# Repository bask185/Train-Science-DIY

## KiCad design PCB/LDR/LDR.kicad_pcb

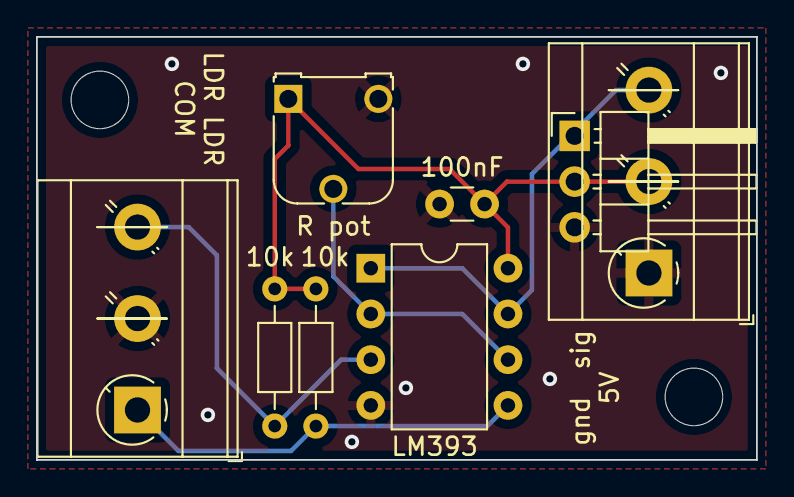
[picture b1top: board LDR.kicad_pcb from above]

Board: 2 copper layers, 40.0 x 23.5 mm, 8 parts (0 on the bottom side), 6 nets.

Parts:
C: 100nF; C_Disc_D3.0mm_W1.6mm_P2.50mm
J1101: LDR; TerminalBlock_MetzConnect_Type073_RT02603HBLU_1x03_P5.08mm_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
J1102: ter; PinHeader_1x03_P2.54mm_Horizontal
J1103: ter; TerminalBlock_MetzConnect_Type073_RT02603HBLU_1x03_P5.08mm_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
R1101, R1102: 10k; R_Axial_DIN0204_L3.6mm_D1.6mm_P7.62mm_Horizontal
R pot: REF; Potentiometer_Runtron_RM-065_Vertical
U1101: LM393; DIP-8_W7.62mm

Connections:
+5V: C.1, J1102.2, J1103.2, R1101.1, R1102.1, R pot.1, U1101.8 (V+)
GND: C.2, J1101.2, J1102.3, J1103.1, R pot.3, U1101.4 (V-)
unnamed: J1101.1, R1101.2, U1101.5 (+)
unnamed: J1101.3, R1102.2, U1101.3 (+)
unnamed: J1102.1, J1103.3, U1101.1, U1101.7
unnamed: R pot.2, U1101.2 (-), U1101.6 (-)

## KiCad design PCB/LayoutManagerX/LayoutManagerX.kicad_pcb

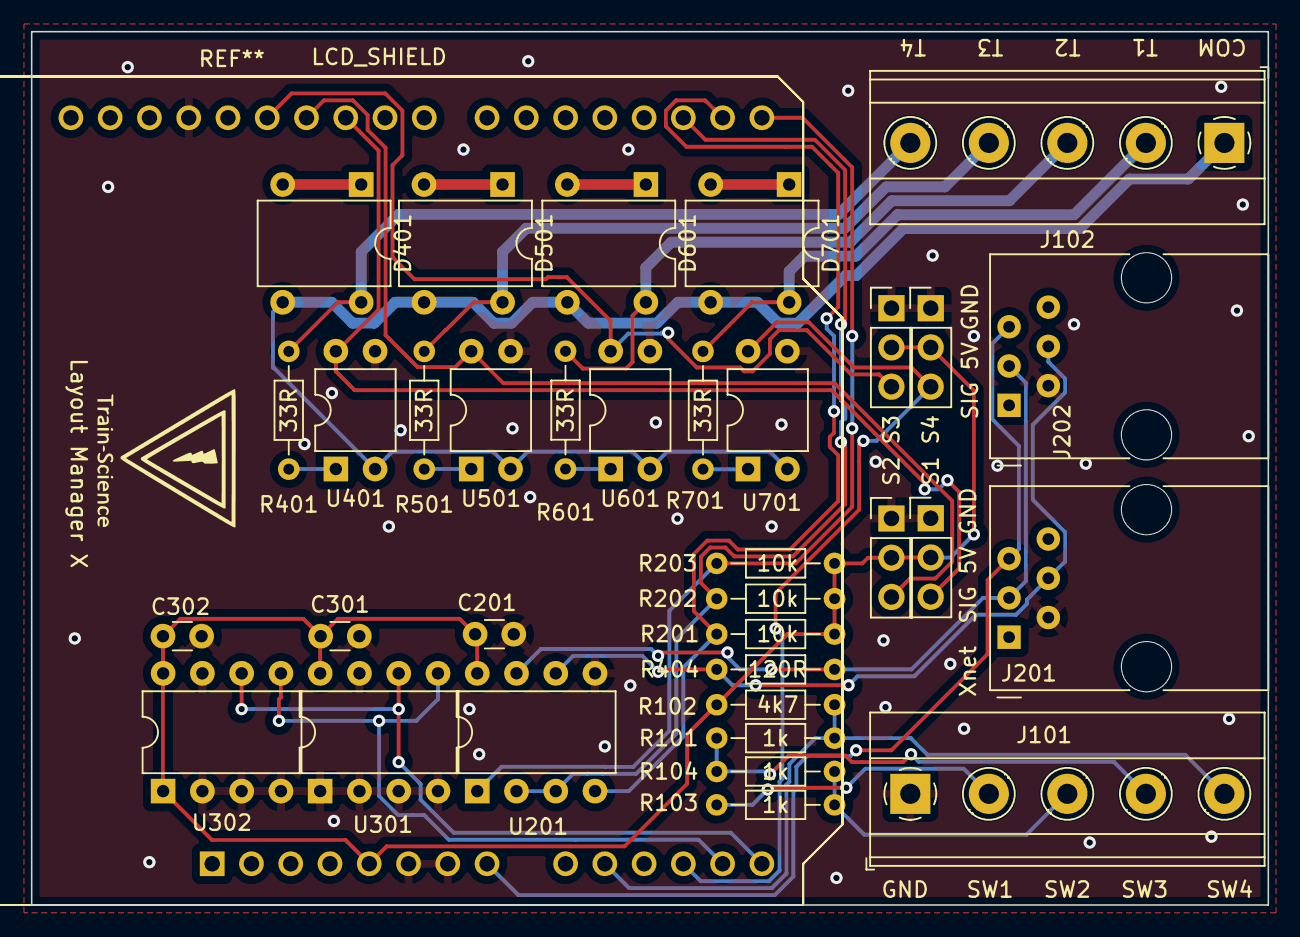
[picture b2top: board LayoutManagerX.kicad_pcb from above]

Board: 2 copper layers, 80.0 x 56.5 mm, 36 parts (0 on the bottom side), 31 nets.

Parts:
A101: Arduino_UNO_R3; UNO_SHIELD_NEUTRAL
C201: C_Disc_D3.0mm_W1.6mm_P2.50mm
C301, C302: 100nF; C_Disc_D3.0mm_W1.6mm_P2.50mm
D401, D501, D601, D701: D_Bridge_+-AA; Diode_Bridge_DIP-4_W7.62mm_P5.08mm
J101, J102: Screw_Terminal_01x05; TerminalBlock_Phoenix_MKDS-1,5-5-5.08_1x05_P5.08mm_Horizont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
J201, J202: RJ12
J402, J501, J601, J701: Conn_01x03_Male; PinHeader_1x03_P2.54mm_Vertical
LCD_SHIELD: UNO_LCD_SHIELD
R101: 4k7; R_Axial_DIN0204_L3.6mm_D1.6mm_P7.62mm_Horizontal
R102, R103, R104: 1k; R_Axial_DIN0204_L3.6mm_D1.6mm_P7.62mm_Horizontal
R201, R202, R203: 10k; R_Axial_DIN0204_L3.6mm_D1.6mm_P7.62mm_Horizontal
R401, R501, R601, R701: 33R; R_Axial_DIN0204_L3.6mm_D1.6mm_P7.62mm_Horizontal
R404: 120R; R_Axial_DIN0204_L3.6mm_D1.6mm_P7.62mm_Horizontal
U201: MAX485E; DIP-8_W7.62mm
U301, U302: 24LC256; DIP-8_W7.62mm
U401, U501, U601, U701: EL814; DIP-4_W7.62mm

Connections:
+5V: A101.5 (+5V), C201.1, C301.1, C302.1, J402.2, J501.2, J601.2, J701.2, R101.2, R201.1, R202.1, R203.1, U201.8 (VCC), U301.8 (VCC), U302.1 (A0), U302.8 (VCC)
+12V: A101.8 (VIN), J201.5, J202.5
/Xnet/485dir: A101.17 (D2), R202.2, U201.2 (~RE), U201.3 (DE)
/Xnet/Rx: A101.15 (D0/RX), R203.2, U201.1 (RO)
/Xnet/Tx: A101.16 (D1/TX), R201.2, U201.4 (DI)
/eeprom/SCL: A101.14 (SCL/A5), U301.6 (SCL), U302.6 (SCL)
/eeprom/SDA: A101.13 (SDA/A4), U301.5 (SDA), U302.5 (SDA)
/input1: A101.25 (D10), J402.3, U401.4
/input2: A101.26 (D11), J501.3, U501.4
/input3: A101.27 (D12), J601.3, U601.4
/input4: A101.12 (A3), J701.3, U701.4
/sensor1/com: D401.3, D501.3, D601.3, D701.3, J102.1, U401.2, U501.2, U601.2, U701.2
/switches: A101.10 (A1), J101.5, R101.1, R102.2
/track1: D401.4, J102.5, R401.1
/track2: D501.4, J102.4, R501.1
/track3: D601.4, J102.3, R601.1
/track4: D701.4, J102.2, R701.1
A: J201.4, J202.4, R404.1, U201.6 (A)
B: J201.3, J202.3, R404.2, U201.7 (B)
GND: A101.6 (GND), A101.7 (GND), A101.29 (GND), C201.2, C301.2, C302.2, J101.1, J201.2, J202.2, J402.1, J501.1, J601.1, J701.1, U201.5 (GND), U301.1 (A0), U301.2 (A1), U301.3 (A2), U301.4 (GND), U301.7 (WP), U302.2 (A1), U302.3 (A2), U302.4 (GND), U302.7 (WP), U401.3, U501.3, U601.3, U701.3
unnamed: D401.1 (+), D401.2 (-)
unnamed: D501.1 (+), D501.2 (-)
unnamed: D601.1 (+), D601.2 (-)
unnamed: D701.1 (+), D701.2 (-)
unnamed: J101.2, R104.1
unnamed: J101.3, R103.1, R104.2
unnamed: J101.4, R102.1, R103.2
unnamed: R401.2, U401.1
unnamed: R501.2, U501.1
unnamed: R601.2, U601.1
unnamed: R701.2, U701.1

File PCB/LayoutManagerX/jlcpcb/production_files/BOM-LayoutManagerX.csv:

Comment,Designator,Footprint,LCSC
~,C201,C_Disc_D3.0mm_W1.6mm_P2.50mm,C14663
10k,"R201,R202,R203",R_Axial_DIN0204_L3.6mm_D1.6mm_P7.62mm_Horizontal,C25744
MAX485E,U201,DIP-8_W7.62mm,C668206
Arduino_UNO_R3,A101,UNO_SHIELD_NEUTRAL,
RJ12,J202,RJ12,
RJ12,J201,RJ12,
D_Bridge_+-AA,D701,Diode_Bridge_DIP-4_W7.62mm_P5.08mm,
100nF,C302,C_Disc_D3.0mm_W1.6mm_P2.50mm,
Screw_Terminal_01x05,J102,"TerminalBlock_Phoenix_MKDS-1,5-5-5.08_1x05_P5.08mm_Horizontal",
Screw_Terminal_01x05,J101,"TerminalBlock_Phoenix_MKDS-1,5-5-5.08_1x05_P5.08mm_Horizontal",
Conn_01x03_Male,J402,PinHeader_1x03_P2.54mm_Vertical,
33R,R601,R_Axial_DIN0204_L3.6mm_D1.6mm_P7.62mm_Horizontal,
1k,R103,R_Axial_DIN0204_L3.6mm_D1.6mm_P7.62mm_Horizontal,
33R,R501,R_Axial_DIN0204_L3.6mm_D1.6mm_P7.62mm_Horizontal,
D_Bridge_+-AA,D601,Diode_Bridge_DIP-4_W7.62mm_P5.08mm,
4k7,R101,R_Axial_DIN0204_L3.6mm_D1.6mm_P7.62mm_Horizontal,
24LC256,U302,DIP-8_W7.62mm,
100nF,C301,C_Disc_D3.0mm_W1.6mm_P2.50mm,
Conn_01x03_Male,J701,PinHeader_1x03_P2.54mm_Vertical,
1k,R102,R_Axial_DIN0204_L3.6mm_D1.6mm_P7.62mm_Horizontal,
EL814,U401,DIP-4_W7.62mm,
EL814,U701,DIP-4_W7.62mm,
D_Bridge_+-AA,D501,Diode_Bridge_DIP-4_W7.62mm_P5.08mm,
Conn_01x03_Male,J601,PinHeader_1x03_P2.54mm_Vertical,
EL814,U601,DIP-4_W7.62mm,
120R,R404,R_Axial_DIN0204_L3.6mm_D1.6mm_P7.62mm_Horizontal,
24LC256,U301,DIP-8_W7.62mm,
Conn_01x03_Male,J501,PinHeader_1x03_P2.54mm_Vertical,
33R,R401,R_Axial_DIN0204_L3.6mm_D1.6mm_P7.62mm_Horizontal,
D_Bridge_+-AA,D401,Diode_Bridge_DIP-4_W7.62mm_P5.08mm,
EL814,U501,DIP-4_W7.62mm,
33R,R701,R_Axial_DIN0204_L3.6mm_D1.6mm_P7.62mm_Horizontal,
1k,R104,R_Axial_DIN0204_L3.6mm_D1.6mm_P7.62mm_Horizontal,

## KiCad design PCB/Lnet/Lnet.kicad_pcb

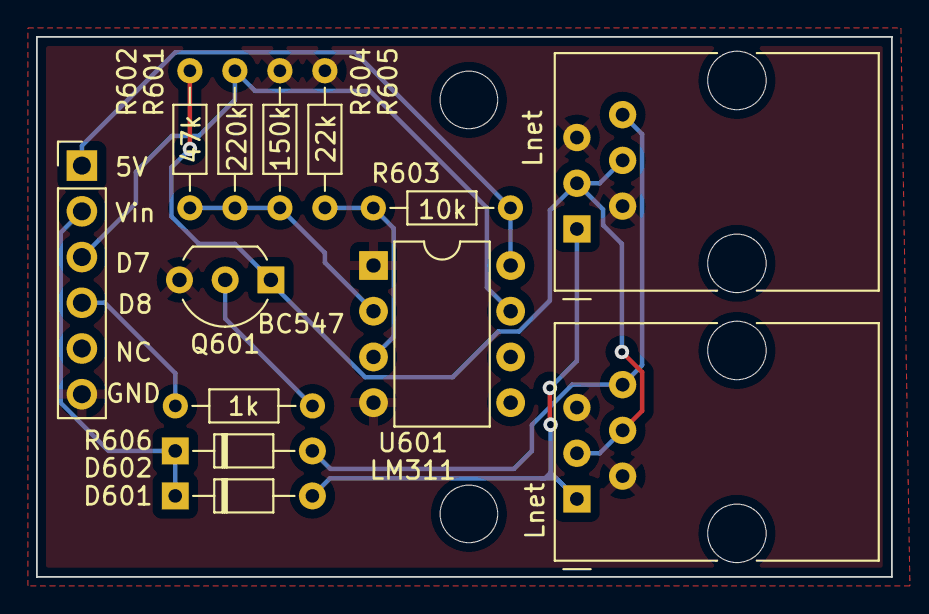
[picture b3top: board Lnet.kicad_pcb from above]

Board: 2 copper layers, 47.5 x 30.0 mm, 13 parts (0 on the bottom side), 11 nets.

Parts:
D601, D602: D; D_DO-34_SOD68_P7.62mm_Horizontal
J601, J602: RJ12; RJ12_Amphenol_54601
J603: Conn_01x06_Male; PinHeader_1x06_P2.54mm_Vertical
Q601: BC547; TO-92_Inline_Wide
R601: 220k; R_Axial_DIN0204_L3.6mm_D1.6mm_P7.62mm_Horizontal
R602: 47k; R_Axial_DIN0204_L3.6mm_D1.6mm_P7.62mm_Horizontal
R603: 10k; R_Axial_DIN0204_L3.6mm_D1.6mm_P7.62mm_Horizontal
R604: 150k; R_Axial_DIN0204_L3.6mm_D1.6mm_P7.62mm_Horizontal
R605: 22k; R_Axial_DIN0204_L3.6mm_D1.6mm_P7.62mm_Horizontal
R606: 1k; R_Axial_DIN0204_L3.6mm_D1.6mm_P7.62mm_Horizontal
U601: LM311; DIP-8_W7.62mm

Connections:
+5V: J603.1, R603.2, U601.8 (V+)
+12V: D601.1 (K), D602.1 (K), J603.2
GND: J601.2, J601.5, J602.2, J602.5, J603.6, Q601.3 (E), R604.1, R605.1, U601.1 (GND), U601.4 (V-)
Lnet_Rx: J603.3, R601.2, U601.7
Lnet_Tx: J603.4, R606.2
unnamed: J601.3, J601.4, J602.3, J602.4, Q601.1 (C), R602.2
unnamed: R601.1, R602.1, R604.2, U601.2 (+)
unnamed: R603.1, R605.2, U601.3 (-)
unnamed: Q601.2 (B), R606.1
railsyncA: D602.2 (A), J601.6, J602.6
railsyncB: D601.2 (A), J601.1, J602.1

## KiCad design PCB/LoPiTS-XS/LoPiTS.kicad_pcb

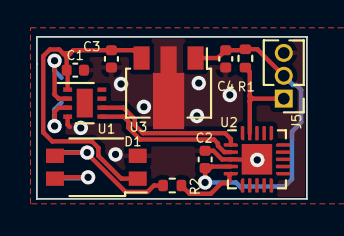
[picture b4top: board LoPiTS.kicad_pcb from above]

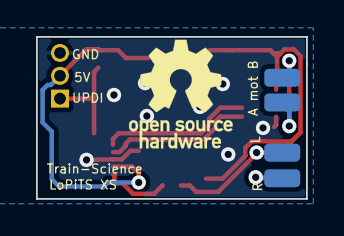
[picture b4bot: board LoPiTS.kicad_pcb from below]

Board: 2 copper layers, 15.0 x 9.0 mm, 15 parts (4 on the bottom side), 11 nets.

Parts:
C1, C2, C4: 100nF; C_0402_1005Metric
C3: 330nF; C_0402_1005Metric
D1: D_Bridge_+-AA; Diode_Bridge_Diotec_MicroDil_3.0x3.0x1.8mm
J1, J2, J3, J4: Conn_01x01_Pin; SolderWirePad_1x01_SMD_1x2mm
J5: Conn_01x03_Pin; PinHeader_1x03_P1.27mm_Vertical
R1: R; R_0402_1005Metric
R2: 33k; R_0402_1005Metric
U1: WSON-8-1EP_2x2mm_P0.5mm_EP0.9x1.6mm
U2: ATtiny416-M; VQFN-20-1EP_3x3mm_P0.4mm_EP1.7x1.7mm
U3: L78L05_SOT89; SOT-89-3

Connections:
/Hbridge/MOT_A: J4.1, U1.2 (OUT1)
/Hbridge/MOT_B: J3.1, U1.3 (OUT2)
/Hbridge/PWM_A: U1.6 (IN1), U2.1 (PA2)
/Hbridge/PWM_B: U1.5 (IN2), U2.2 (PA3)
/Hbridge/VCC: C1.2, C3.1, D1.1 (+), U1.1 (VM), U3.3 (IN)
/attiny/5V: C2.2, C4.1, J5.2, R1.1, U2.4 (VCC), U3.1 (OUT)
/attiny/DCC_IN: R2.1, U2.5 (PA4)
/attiny/UPDI: J5.1, R1.2, U2.19 (~RESET/PA0)
/regulator/DCC_A: D1.3, J1.1, R2.2
/regulator/DCC_B: D1.4, J2.1
GND: C1.1, C2.1, C3.2, C4.2, D1.2 (-), J5.3, U1.4 (GND), U2.3 (GND), U2.21 (GND), U3.2 (GND)

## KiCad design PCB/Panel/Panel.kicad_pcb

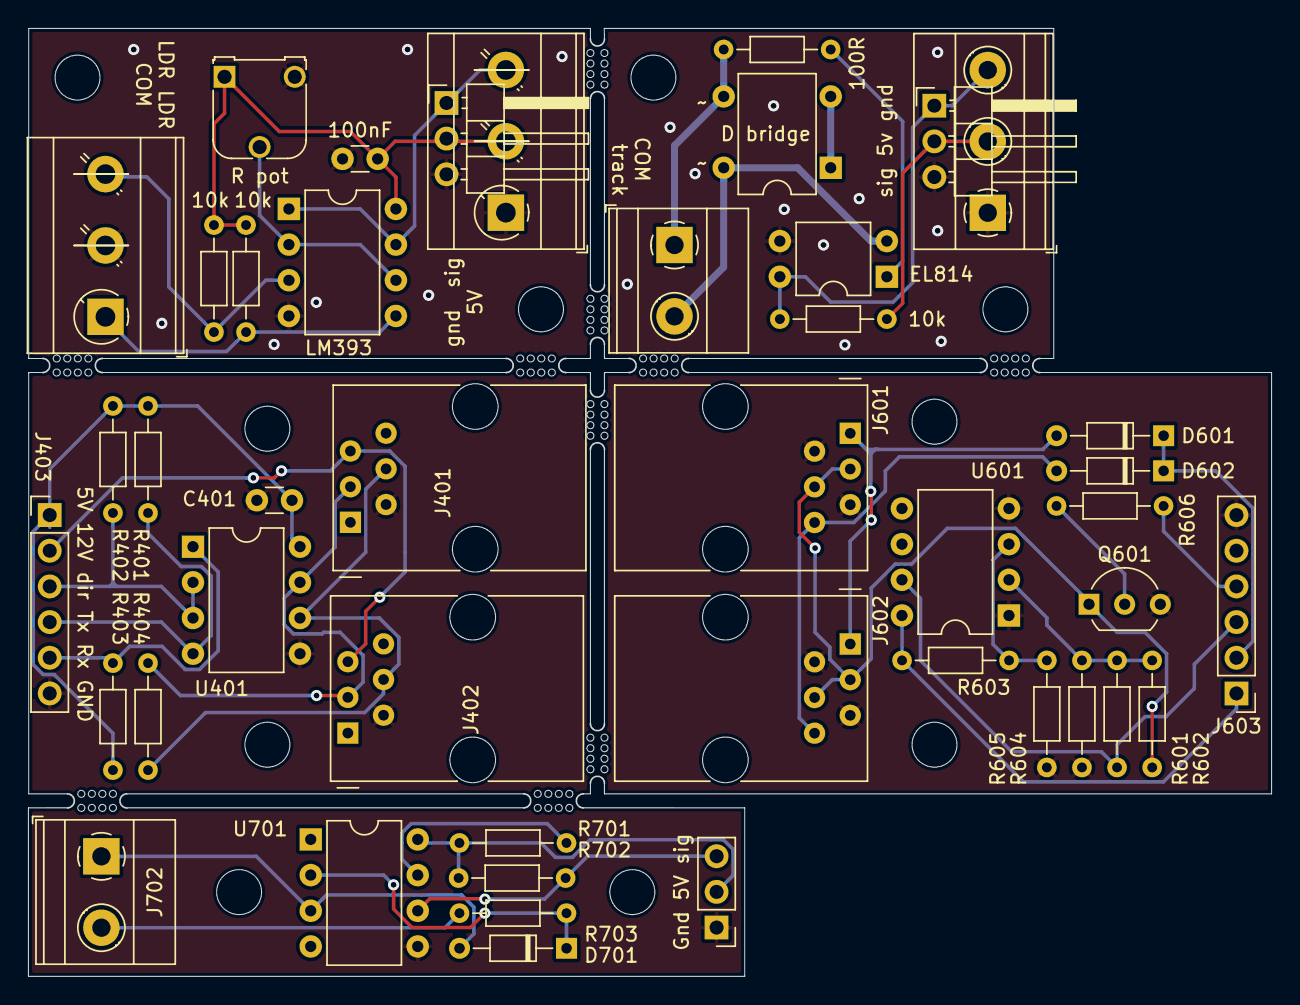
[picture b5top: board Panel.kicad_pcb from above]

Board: 2 copper layers, 88.5 x 67.5 mm, 44 parts (0 on the bottom side), 7 nets.

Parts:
C: 100nF; C_Disc_D3.0mm_W1.6mm_P2.50mm
C401: 100n; C_Disc_D3.0mm_W1.6mm_P2.50mm
D601, D602, D701: D; D_DO-34_SOD68_P7.62mm_Horizontal
D1201: D; Diode_Bridge_DIP-4_W7.62mm_P5.08mm
J401, J402, J601, J602: RJ12; RJ12_Amphenol_54601
J403, J603: Conn_01x06_Male; PinHeader_1x06_P2.54mm_Vertical
J701: Conn_01x03_Male; PinHeader_1x03_P2.54mm_Vertical
J702: Screw_Terminal_01x02; TerminalBlock_Phoenix_MKDS-1,5-2-5.08_1x02_P5.08mm_Horizont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
J1101: LDR; TerminalBlock_MetzConnect_Type073_RT02603HBLU_1x03_P5.08mm_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
J1102, J1203: ter; PinHeader_1x03_P2.54mm_Horizontal
J1103: ter; TerminalBlock_MetzConnect_Type073_RT02603HBLU_1x03_P5.08mm_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
J1201: tracks; TerminalBlock_Phoenix_MKDS-1,5-2-5.08_1x02_P5.08mm_Horizont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
J1202: ter; TerminalBlock_Phoenix_MKDS-1,5-3-5.08_1x03_P5.08mm_Horizont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
Q601: BC547; TO-92_Inline_Wide
R401, R402, R403, R603, R701, R702, R1101, R1102, R1202: 10k; R_Axial_DIN0204_L3.6mm_D1.6mm_P7.62mm_Horizontal
R404: 120R; R_Axial_DIN0204_L3.6mm_D1.6mm_P7.62mm_Horizontal
R601: 220k; R_Axial_DIN0204_L3.6mm_D1.6mm_P7.62mm_Horizontal
R602: 47k; R_Axial_DIN0204_L3.6mm_D1.6mm_P7.62mm_Horizontal
R604: 150k; R_Axial_DIN0204_L3.6mm_D1.6mm_P7.62mm_Horizontal
R605: 22k; R_Axial_DIN0204_L3.6mm_D1.6mm_P7.62mm_Horizontal
R606, R703: 1k; R_Axial_DIN0204_L3.6mm_D1.6mm_P7.62mm_Horizontal
R1201: 100R; R_Axial_DIN0204_L3.6mm_D1.6mm_P7.62mm_Horizontal
R pot: REF; Potentiometer_Runtron_RM-065_Vertical
U401: MAX485E; DIP-8_W7.62mm
U601: LM311; DIP-8_W7.62mm
U701: 6N137; DIP-8_W7.62mm
U1101: LM393; DIP-8_W7.62mm
U1201: EL814; DIP-4_W7.62mm

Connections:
+5V: C.1, C401.1, J403.1, J603.1, J701.2, J1102.2, J1103.2, J1202.2, J1203.2, R401.2, R402.2, R403.2, R603.2, R701.1, R702.1, R1101.1, R1102.1, R1202.1, R pot.1, U401.8 (VCC), U601.8 (V+), U701.8 (VCC), U1101.8 (V+)
DCC-A: J702.2, R703.1
DCC-B: D701.2 (A), J702.1, U701.3 (C)
DCC_IN: J701.3, R702.2, U701.6 (VO)
GND: C.2, C401.2, J401.2, J402.2, J403.6, J601.2, J601.5, J602.2, J602.5, J603.6, J701.1, J1101.2, J1102.3, J1103.1, J1202.1, J1203.3, Q601.3 (E), R604.1, R605.1, R pot.3, U401.5 (GND), U601.1 (GND), U601.4 (V-), U701.5 (GND), U1101.4 (V-), U1201.3
unnamed: D701.1 (K), R703.2, U701.2 (A)
unnamed: R701.2, U701.7 (EN)

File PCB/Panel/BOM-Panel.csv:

Comment,Designator,Footprint,LCSC
6N137,U701,DIP-8_W7.62mm,C110020
D,"D601,D602",D_DO-34_SOD68_P7.62mm_Horizontal,C14996
10k,"R701,R702",R_Axial_DIN0204_L3.6mm_D1.6mm_P7.62mm_Horizontal,C17414
1k,R703,R_Axial_DIN0204_L3.6mm_D1.6mm_P7.62mm_Horizontal,C17513
LM311,U601,DIP-8_W7.62mm,C434495
RJ12,"J601,J602",RJ12_Amphenol_54601,C77859
LDR,J1101,TerminalBlock_MetzConnect_Type073_RT02603HBLU_1x03_P5.08mm_Horizontal,
Conn_01x06_Male,J403,PinHeader_1x06_P2.54mm_Vertical,
tracks,J1201,"TerminalBlock_Phoenix_MKDS-1,5-2-5.08_1x02_P5.08mm_Horizontal",
ter,J1202,"TerminalBlock_Phoenix_MKDS-1,5-3-5.08_1x03_P5.08mm_Horizontal",
ter,J1103,TerminalBlock_MetzConnect_Type073_RT02603HBLU_1x03_P5.08mm_Horizontal,
Conn_01x03_Male,J701,PinHeader_1x03_P2.54mm_Vertical,
47k,R602,R_Axial_DIN0204_L3.6mm_D1.6mm_P7.62mm_Horizontal,
RJ12,J401,RJ12_Amphenol_54601,
10k,R401,R_Axial_DIN0204_L3.6mm_D1.6mm_P7.62mm_Horizontal,
10k,R603,R_Axial_DIN0204_L3.6mm_D1.6mm_P7.62mm_Horizontal,
EL814,U1201,DIP-4_W7.62mm,
10k,R1101,R_Axial_DIN0204_L3.6mm_D1.6mm_P7.62mm_Horizontal,
100R,R1201,R_Axial_DIN0204_L3.6mm_D1.6mm_P7.62mm_Horizontal,
BC547,Q601,TO-92_Inline_Wide,
D,D701,D_DO-34_SOD68_P7.62mm_Horizontal,
RJ12,J402,RJ12_Amphenol_54601,
150k,R604,R_Axial_DIN0204_L3.6mm_D1.6mm_P7.62mm_Horizontal,
120R,R404,R_Axial_DIN0204_L3.6mm_D1.6mm_P7.62mm_Horizontal,
10k,R1102,R_Axial_DIN0204_L3.6mm_D1.6mm_P7.62mm_Horizontal,
D,D1201,Diode_Bridge_DIP-4_W7.62mm_P5.08mm,
10k,R403,R_Axial_DIN0204_L3.6mm_D1.6mm_P7.62mm_Horizontal,
MAX485E,U401,DIP-8_W7.62mm,
Conn_01x06_Male,J603,PinHeader_1x06_P2.54mm_Vertical,
Screw_Terminal_01x02,J702,"TerminalBlock_Phoenix_MKDS-1,5-2-5.08_1x02_P5.08mm_Horizontal",
LM393,U1101,DIP-8_W7.62mm,
10k,R402,R_Axial_DIN0204_L3.6mm_D1.6mm_P7.62mm_Horizontal,
22k,R605,R_Axial_DIN0204_L3.6mm_D1.6mm_P7.62mm_Horizontal,
ter,J1203,PinHeader_1x03_P2.54mm_Horizontal,
10k,R1202,R_Axial_DIN0204_L3.6mm_D1.6mm_P7.62mm_Horizontal,
220k,R601,R_Axial_DIN0204_L3.6mm_D1.6mm_P7.62mm_Horizontal,
ter,J1102,PinHeader_1x03_P2.54mm_Horizontal,
100n,C401,C_Disc_D3.0mm_W1.6mm_P2.50mm,
1k,R606,R_Axial_DIN0204_L3.6mm_D1.6mm_P7.62mm_Horizontal,

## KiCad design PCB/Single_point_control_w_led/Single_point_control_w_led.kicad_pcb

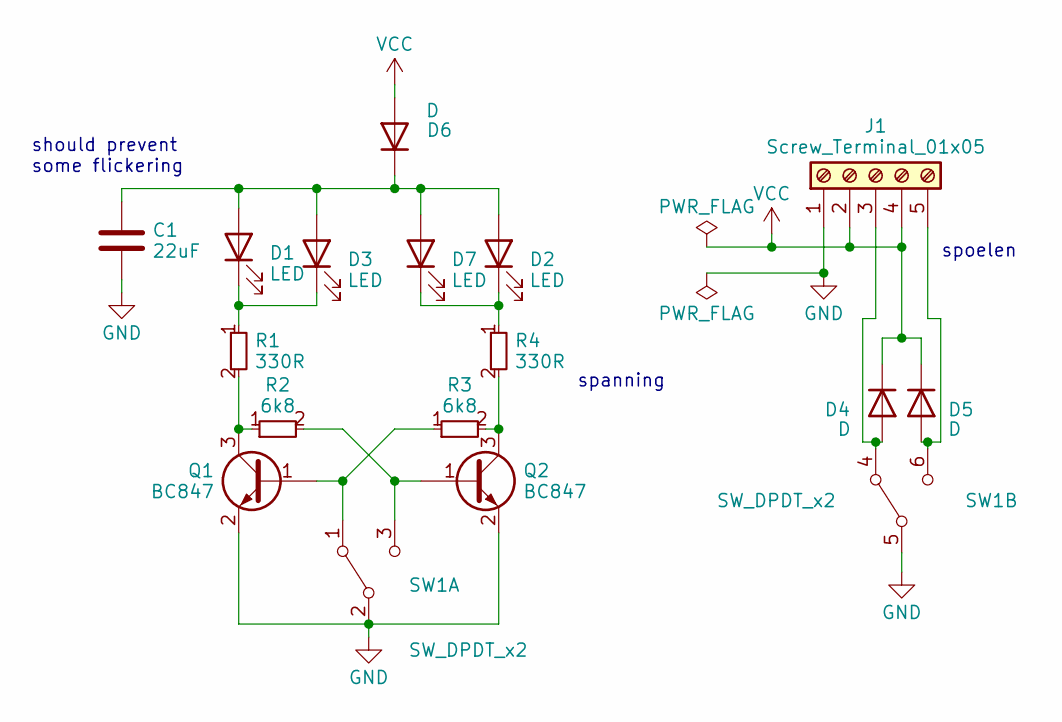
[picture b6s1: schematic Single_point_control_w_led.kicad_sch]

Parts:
C1: 22uF; C_1206_3216Metric; JLCPCB Part# C12891
D1, D2, D3, D7: LED; LED_D3.0mm
D4, D5, D6: D; D_SOD-123F; JLCPCB Part# C64898
J1: Screw_Terminal_01x05; TerminalBlock_Phoenix_MKDS-1,5-5-5.08_1x05_P5.08mm_Horizont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
Q1, Q2: BC847; SOT-23; JLCPCB Part# C475630
R1, R4: 330R; R_0805_handsolder-smalltext; JLCPCB Part# C17630
R2, R3: 6k8; R_0805_handsolder-smalltext; JLCPCB Part# C17772
SW1: SW_DPDT_x2; MTS_DPDT

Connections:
GND: C1.2, J1.1, Q1.2 (E), Q2.2 (E), SW1.2 (B), SW1.5 (B)
unnamed: C1.1, D1.2 (A), D2.2 (A), D3.2 (A), D6.1 (K), D7.2 (A)
unnamed: D1.1 (K), D3.1 (K), R1.1
unnamed: D2.1 (K), D7.1 (K), R4.1
unnamed: D4.2 (A), J1.3, SW1.4 (A)
unnamed: D5.2 (A), J1.5, SW1.6 (C)
unnamed: Q1.1 (B), R3.1, SW1.1 (A)
unnamed: Q1.3 (C), R1.2, R2.1
unnamed: Q2.1 (B), R2.2, SW1.3 (C)
unnamed: Q2.3 (C), R3.2, R4.2
VCC: D4.1 (K), D5.1 (K), D6.2 (A), J1.2, J1.4

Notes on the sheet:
spoelen
spanning
should prevent some flickering

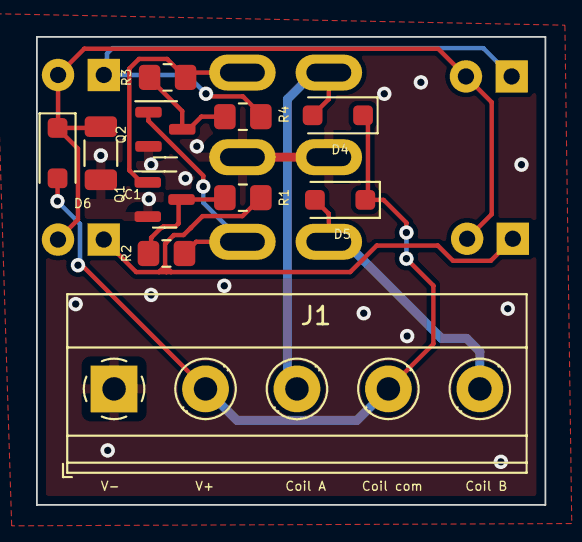
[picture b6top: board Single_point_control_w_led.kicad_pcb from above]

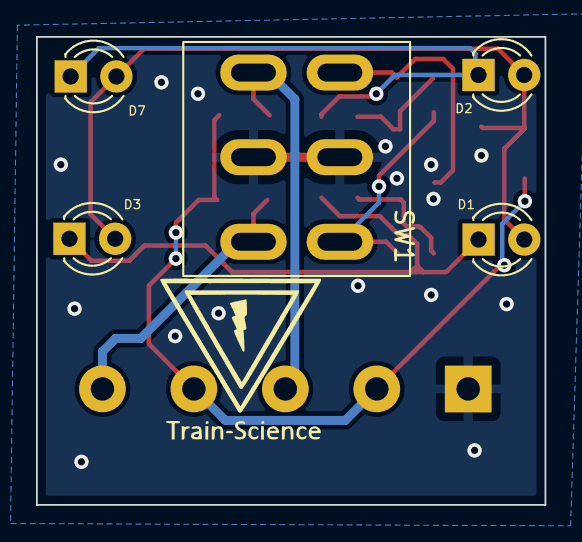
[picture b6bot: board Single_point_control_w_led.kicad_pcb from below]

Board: 2 copper layers, 28.2 x 26.0 mm, 16 parts (5 on the bottom side), 11 nets.

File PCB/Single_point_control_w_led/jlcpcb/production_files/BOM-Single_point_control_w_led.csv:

Comment,Designator,Footprint,LCSC
22uF,C1,C_1206_3216Metric,C12891
330R,"R1,R4",R_0805_handsolder-smalltext,C17630
6k8,"R2,R3",R_0805_handsolder-smalltext,C17772
BC847,"Q1,Q2",SOT-23,C475630
D,"D4,D5,D6",D_SOD-123F,C64898
LED,D3,LED_D3.0mm,
SW_DPDT_x2,SW1,MTS_DPDT,
Screw_Terminal_01x05,J1,"TerminalBlock_Phoenix_MKDS-1,5-5-5.08_1x05_P5.08mm_Horizontal",
LED,D2,LED_D3.0mm,
LED,D1,LED_D3.0mm,
LED,D7,LED_D3.0mm,

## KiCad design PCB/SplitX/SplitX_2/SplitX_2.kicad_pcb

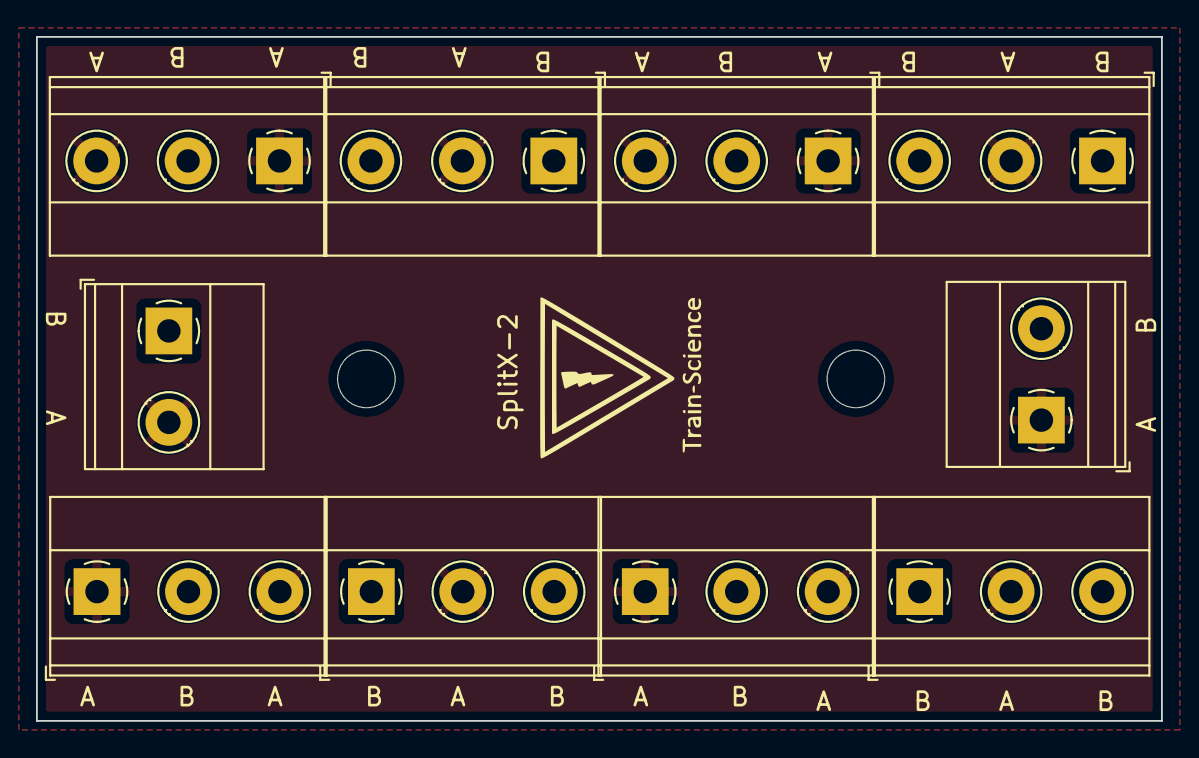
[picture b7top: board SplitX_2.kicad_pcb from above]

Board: 2 copper layers, 62.5 x 38.0 mm, 10 parts (0 on the bottom side), 2 nets, no tracks yet.

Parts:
J1, J10: Screw_Terminal_01x02; TerminalBlock_Phoenix_MKDS-1,5-2-5.08_1x02_P5.08mm_Horizont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
J2, J3, J4, J5, J7, J8, J9: Screw_Terminal_01x03; TerminalBlock_Phoenix_MKDS-1,5-3-5.08_1x03_P5.08mm_Horizont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
Je: Screw_Terminal_01x03; TerminalBlock_Phoenix_MKDS-1,5-3-5.08_1x03_P5.08mm_Horizont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

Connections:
A: J1.2, J2.2, J3.1, J3.3, J4.1, J4.3, J5.2, J7.1, J7.3, J8.1, J8.3, J9.2, J10.1, Je.2
B: J1.1, J2.1, J2.3, J3.2, J4.2, J5.1, J5.3, J7.2, J8.2, J9.1, J9.3, J10.2, Je.1, Je.3

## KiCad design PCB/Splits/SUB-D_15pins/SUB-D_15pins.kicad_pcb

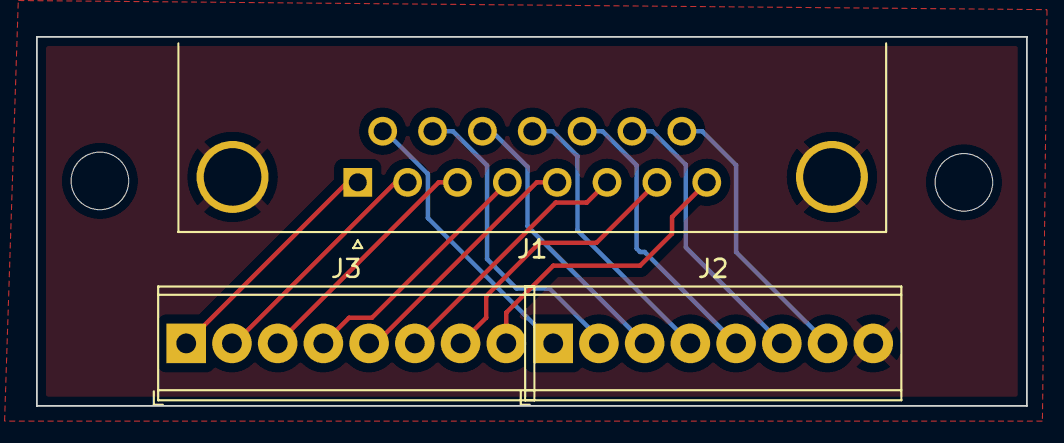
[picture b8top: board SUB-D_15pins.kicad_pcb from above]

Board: 2 copper layers, 55.0 x 20.5 mm, 3 parts (0 on the bottom side), 16 nets.

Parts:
J1: DB15_Female_MountingHoles; DSUB-15_Female_Horizontal_P2.77x2.84mm_EdgePinOffset4.94mm_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
J2, J3: Screw_Terminal_01x08; TerminalBlock_Phoenix_MPT-0,5-8-2.54_1x08_P2.54mm_Horizontal

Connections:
/_1: J1.1, J3.1
/_2: J1.2, J3.2
/_3: J1.3, J3.3
/_4: J1.4, J3.4
/_5: J1.5, J3.5
/_6: J1.6, J3.6
/_7: J1.7, J3.7
/_8: J1.8, J3.8
/_9: J1.9, J2.1
/_10: J1.10, J2.2
/_11: J1.11 (P111), J2.3
/_12: J1.12, J2.4
/_13: J1.13, J2.5
/_14: J1.14, J2.6
/_15: J1.15, J2.7
GND: J1.0 (PAD), J2.8

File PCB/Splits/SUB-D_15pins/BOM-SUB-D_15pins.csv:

Comment,Designator,Footprint,LCSC
Screw_Terminal_01x08,J3,"TerminalBlock_Phoenix_MPT-0,5-8-2.54_1x08_P2.54mm_Horizontal",
Screw_Terminal_01x08,J2,"TerminalBlock_Phoenix_MPT-0,5-8-2.54_1x08_P2.54mm_Horizontal",
DB15_Female_MountingHoles,J1,DSUB-15_Female_Horizontal_P2.77x2.84mm_EdgePinOffset4.94mm_Housed_MountingHolesOffset7.48mm,
